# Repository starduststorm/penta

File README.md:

# penta

PCB designs and code for a Five-pointed star circumscribed within a circle of 55 pixels, for a total of 5³=125 pixels.

## Controls

The Five through-hole circles on the penta are touch-reactive and used to set the pattern.

## Hardware

* RP2040 dual-core ARM processor
* T3902 microphone
* WS2812B-1010 pixels

# Project layout

* board/ contains the KiCad pcb project
* src/ all project-specific source
* lib/ a skeleton copy of [kissfft], and submodule dependency *dustlib*

The project is built using [PlatformIO] in Visual Studio Code.

## Building

Build the v2 environment in the [PlatformIO] project, which corresponds to the MakerFaire2025 hardware.

You will likely need to run
```
git submodule update --init
```
in the source after ```git clone``` in order to fetch the submodule for building.

### Libraries & Dependencies
PlatformIO should fetch the apprpriate version of each dependency on first build.

* [FastLED] - A library for fast 8-bit math and rendering colors onto pixels
* [kissfft] - A simple library used to compute an fft on audio samples
* [dustlib] - My work-in-progress pixel library

[FastLED]: https://github.com/FastLED/FastLED
[PlatformIO]: <https://platformio.org>
[kissfft]: <https://github.com/mborgerding/kissfft>
[dustlib]: <https://github.com/starduststorm/dustlib>

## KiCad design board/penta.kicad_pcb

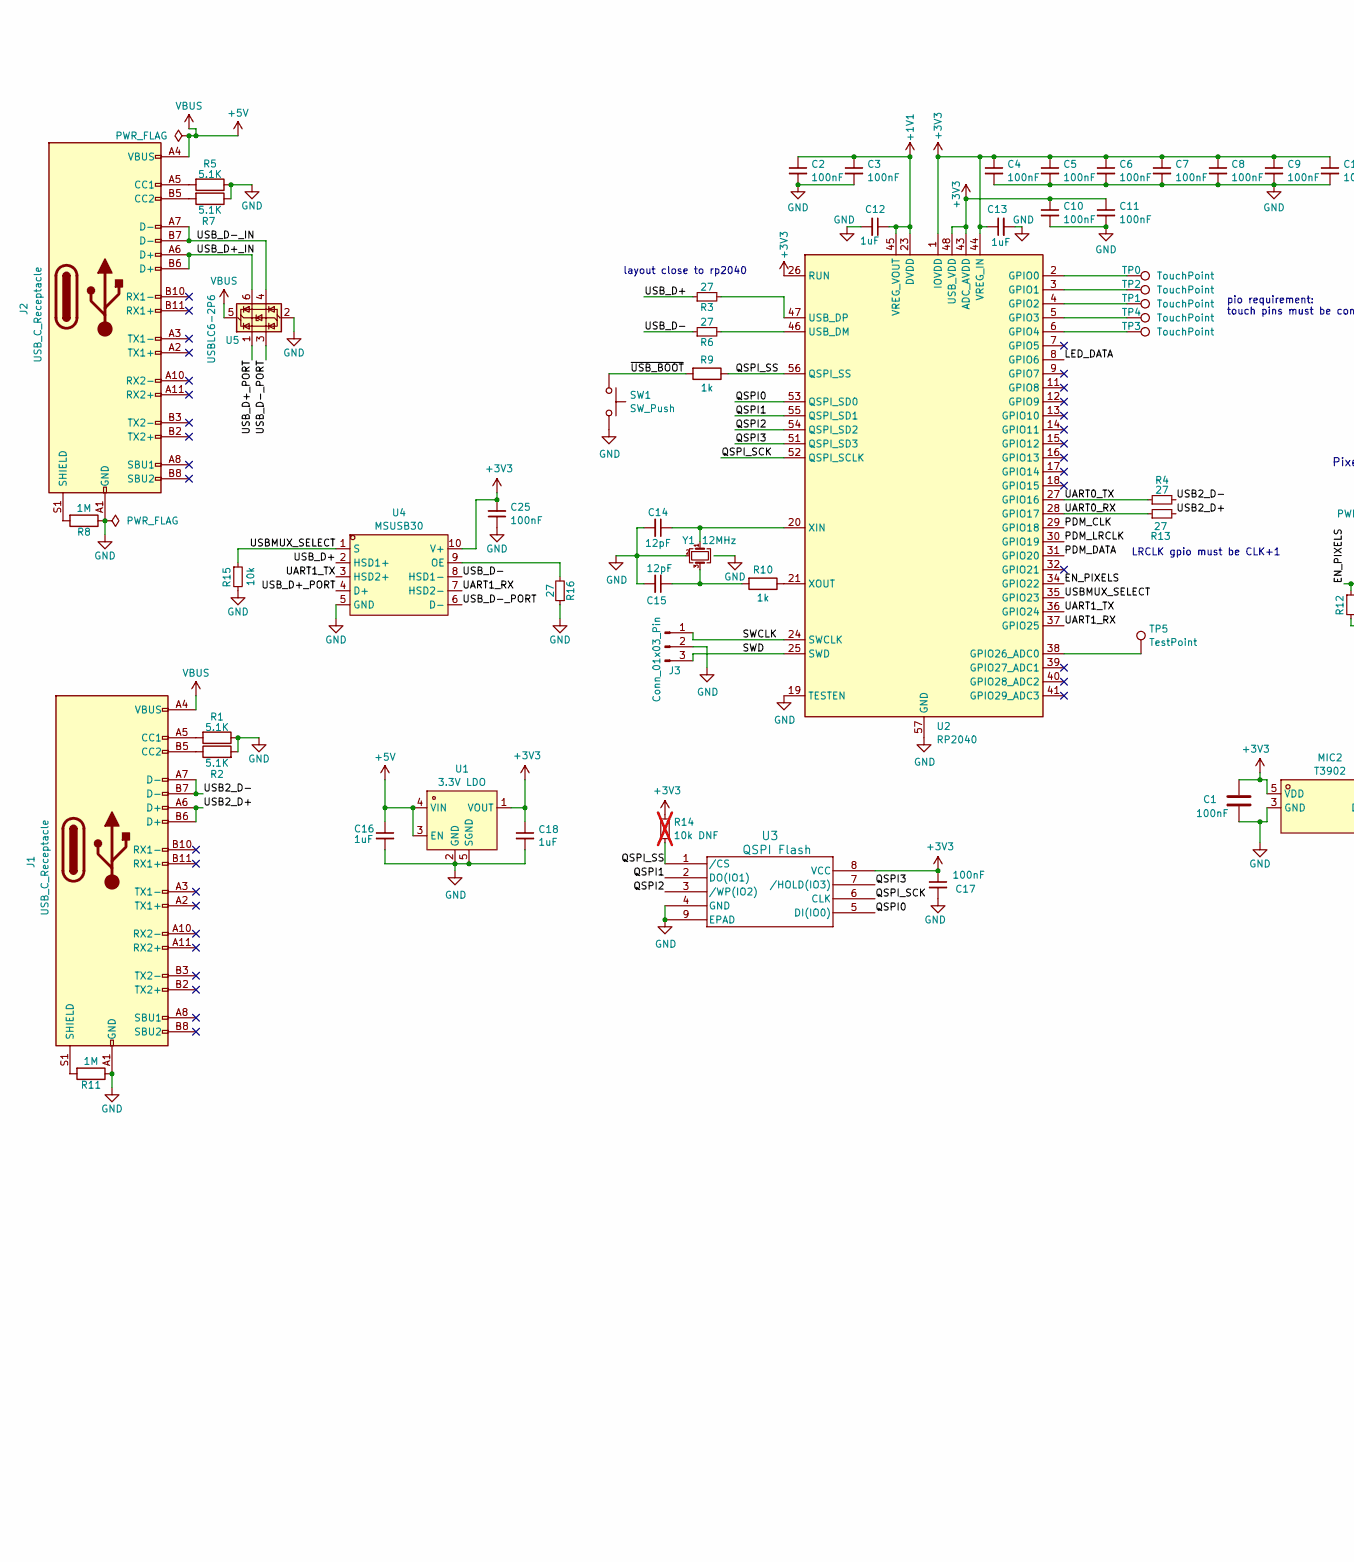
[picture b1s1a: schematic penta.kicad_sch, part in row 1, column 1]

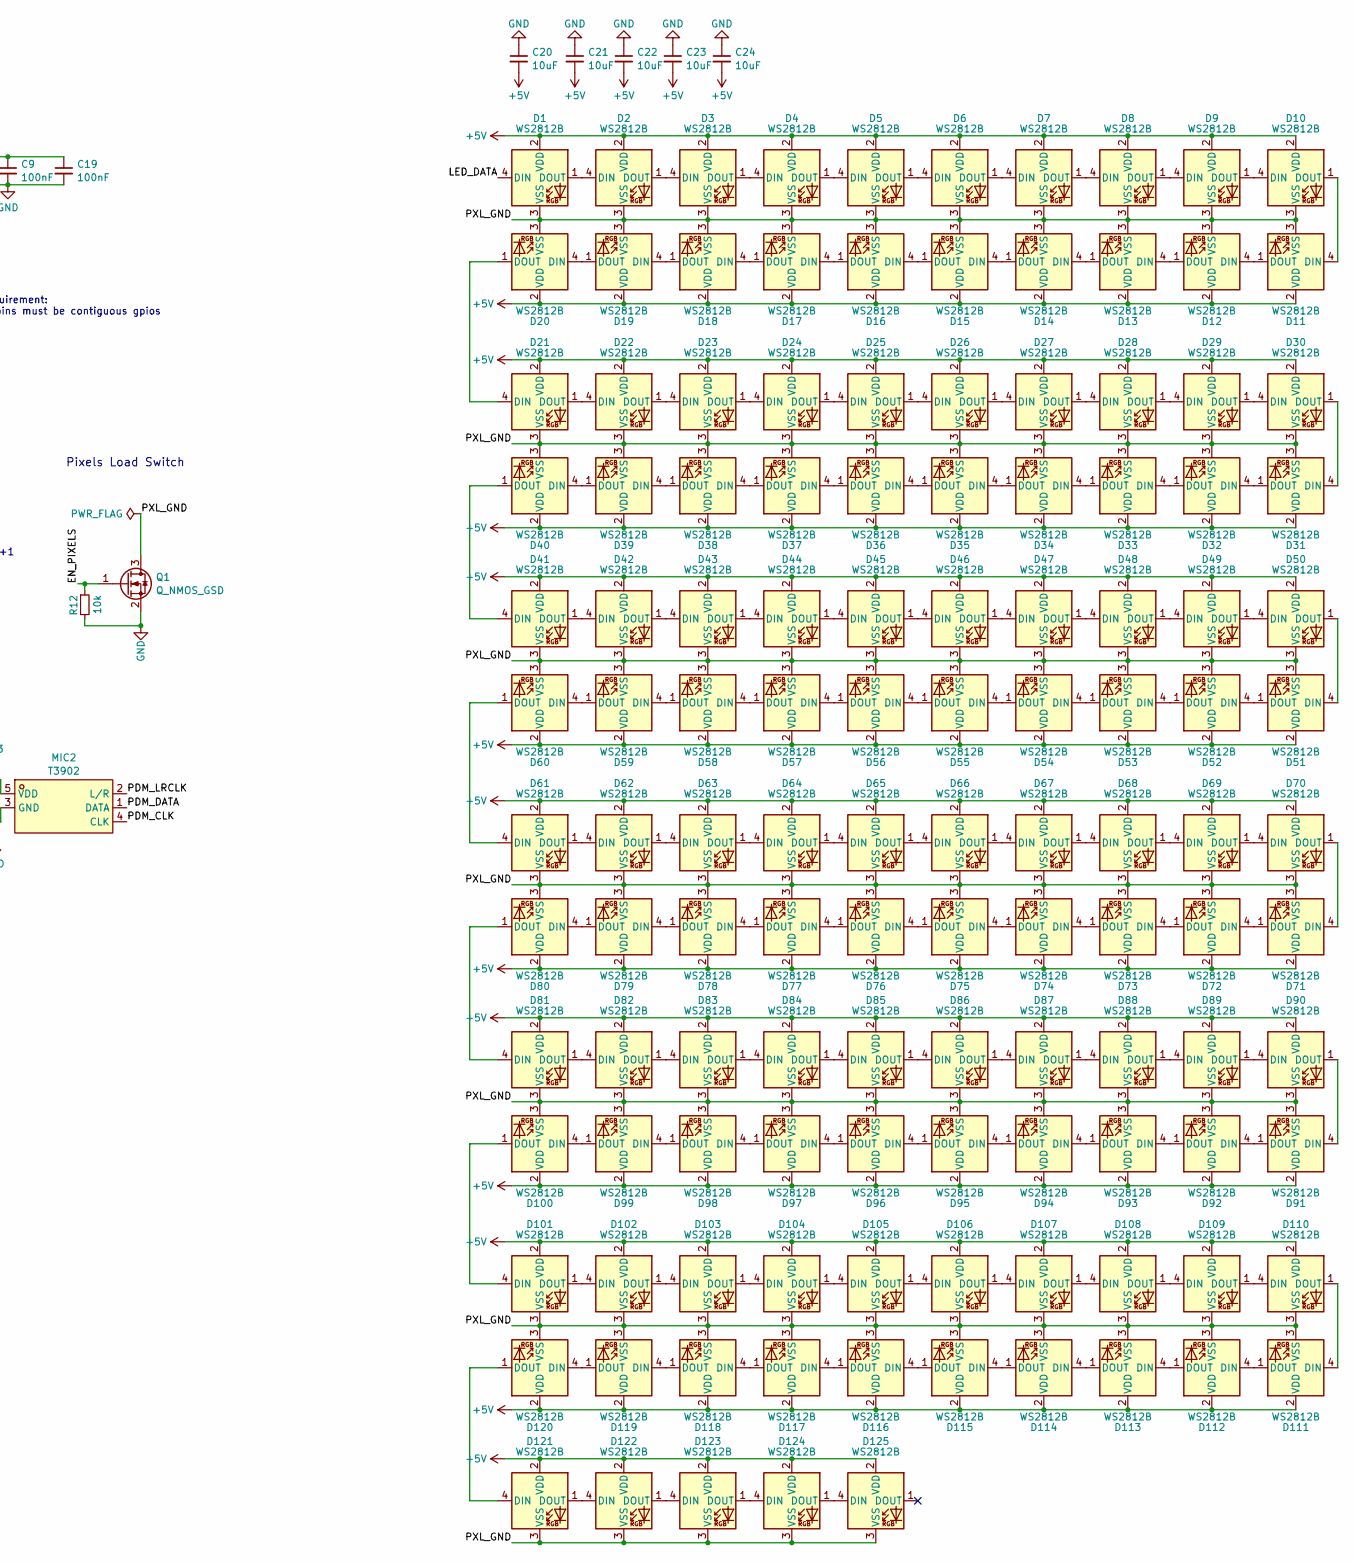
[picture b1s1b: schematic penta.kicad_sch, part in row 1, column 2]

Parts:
C1, C2, C3, C4, C5, C6, C7, C8, C9, C10, C11, C17, C19, C25: 100nF; C_0402_1005Metric; LCSC C1525
C12, C13, C16, C18: 1uF; C_0402_1005Metric; LCSC C52923
C14, C15: 12pF; C_0402_1005Metric; LCSC C1547
C20, C21, C22, C23, C24: 10uF; C_0402_1005Metric; LCSC C15525
D1, D2, D3, D4, D5, D6, D7, D8, D9, D10, D11, D12, D13, D14, D15, D16, D17, D18, D19, D20, D21, D22, D23, D24, D25, D26, D27, D28, D29, D30, D31, D32, D33, D34, D35, D36, D37, D38, D39, D40, D41, D42, D43, D44, D45, D46, D47, D48, D49, D50, D51, D52, D53, D54, D55, D56, D57, D58, D59, D60, D61, D62, D63, D64, D65, D66, D67, D68, D69, D70, D71, D72, D73, D74, D75, D76, D77, D78, D79, D80, D81, D82, D83, D84, D85, D86, D87, D88, D89, D90, D91, D92, D93, D94, D95, D96, D97, D98, D99, D100, D101, D102, D103, D104, D105, D106, D107, D108, D109, D110, D111, D112, D113, D114, D115, D116, D117, D118, D119, D120, D121, D122, D123, D124, D125: WS2812B; ws2812b_1010; LCSC C5349953
J1, J2: USB_C_Receptacle; USB-SMD_USB-TYPE-C-020; LCSC C2927040
J3: Conn_01x03_Pin; SMD_Pad_01x03_1.27mm
MIC2: T3902; MIC_T3902; LCSC Part C3171752
Q1: Q_NMOS_GSD; SOT-23
R1, R2, R5, R7: 5.1K; R_0402_1005Metric; LCSC C25905
R3, R4, R6, R13, R16: 27; R_0402_1005Metric; LCSC C138021
R8, R11: 1M; R_0402_1005Metric; LCSC C26083
R9, R10: 1k; R_0402_1005Metric; LCSC C11702
R12, R15: 10k; R_0402_1005Metric; LCSC C25744
R14: 10k DNF; R_0402_1005Metric; not fitted
SW1: SW_Push; KEY-SMD_L3.0-W2.5-LS4.0; LCSC C2905190
TP0, TP1, TP2, TP3, TP4: TouchPoint; ScrewTouchHole
TP5: TestPoint; TestPoint_Pad_D1.0mm
U1: 3.3V LDO; OnSemi_XDFN4-1EP_1.0x1.0mm_EP0.52x0.52mm; LCSC Part C147954
U2: RP2040; QFN-56-1EP_7x7mm_P0.4mm_EP3.2x3.2mm; LCSC C2040
U3: QSPI Flash; USON_3X2_WIN; LCSC C7304007
U4: MSUSB30; MSOP-10_3x3mm_P0.5mm; LCSC Part C231929
U5: USBLC6-2P6; SOT-666; LCSC C2827693
Y1: 12MHz; Crystal_SMD_2520-4Pin_2.5x2.0mm; LCSC C284155

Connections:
+1V1: C2.1, C3.1, C12.1, U2.23 (DVDD), U2.45 (VREG_VOUT), U2.50 (DVDD)
+3V3: C1.1, C4.1, C5.1, C6.1, C7.1, C8.1, C9.1, C10.1, C11.1, C13.1, C17.1, C18.1, C19.1, C25.2, MIC2.5 (VDD), R14.1, U1.1 (VOUT), U2.1 (IOVDD), U2.10 (IOVDD), U2.22 (IOVDD), U2.26 (RUN), U2.33 (IOVDD), U2.42 (IOVDD), U2.43 (ADC_AVDD), U2.44 (VREG_IN), U2.48 (USB_VDD), U2.49 (IOVDD), U3.8 (VCC), U4.10 (V+)
+5V: C16.1, C20.2, C21.2, C22.2, C23.2, C24.2, D1.2 (VDD), D2.2 (VDD), D3.2 (VDD), D4.2 (VDD), D5.2 (VDD), D6.2 (VDD), D7.2 (VDD), D8.2 (VDD), D9.2 (VDD), D10.2 (VDD), D11.2 (VDD), D12.2 (VDD), D13.2 (VDD), D14.2 (VDD), D15.2 (VDD), D16.2 (VDD), D17.2 (VDD), D18.2 (VDD), D19.2 (VDD), D20.2 (VDD), D21.2 (VDD), D22.2 (VDD), D23.2 (VDD), D24.2 (VDD), D25.2 (VDD), D26.2 (VDD), D27.2 (VDD), D28.2 (VDD), D29.2 (VDD), D30.2 (VDD), D31.2 (VDD), D32.2 (VDD), D33.2 (VDD), D34.2 (VDD), D35.2 (VDD), D36.2 (VDD), D37.2 (VDD), D38.2 (VDD), D39.2 (VDD), D40.2 (VDD), D41.2 (VDD), D42.2 (VDD), D43.2 (VDD), D44.2 (VDD), D45.2 (VDD), D46.2 (VDD), D47.2 (VDD), D48.2 (VDD), D49.2 (VDD), D50.2 (VDD), D51.2 (VDD), D52.2 (VDD), D53.2 (VDD), D54.2 (VDD), D55.2 (VDD), D56.2 (VDD), D57.2 (VDD), D58.2 (VDD), D59.2 (VDD), D60.2 (VDD), D61.2 (VDD), D62.2 (VDD), D63.2 (VDD), D64.2 (VDD), D65.2 (VDD), D66.2 (VDD), D67.2 (VDD), D68.2 (VDD), D69.2 (VDD), D70.2 (VDD), D71.2 (VDD), D72.2 (VDD), D73.2 (VDD), D74.2 (VDD), D75.2 (VDD), D76.2 (VDD), D77.2 (VDD), D78.2 (VDD), D79.2 (VDD), D80.2 (VDD), D81.2 (VDD), D82.2 (VDD), D83.2 (VDD), D84.2 (VDD), D85.2 (VDD), D86.2 (VDD), D87.2 (VDD), D88.2 (VDD), D89.2 (VDD), D90.2 (VDD), D91.2 (VDD), D92.2 (VDD), D93.2 (VDD), D94.2 (VDD), D95.2 (VDD), D96.2 (VDD), D97.2 (VDD), D98.2 (VDD), D99.2 (VDD), D100.2 (VDD), D101.2 (VDD), D102.2 (VDD), D103.2 (VDD), D104.2 (VDD), D105.2 (VDD), D106.2 (VDD), D107.2 (VDD), D108.2 (VDD), D109.2 (VDD), D110.2 (VDD), D111.2 (VDD), D112.2 (VDD), D113.2 (VDD), D114.2 (VDD), D115.2 (VDD), D116.2 (VDD), D117.2 (VDD), D118.2 (VDD), D119.2 (VDD), D120.2 (VDD), D121.2 (VDD), D122.2 (VDD), D123.2 (VDD), D124.2 (VDD), D125.2 (VDD), J1.A4 (VBUS), J1.A9 (VBUS), J1.B4 (VBUS), J1.B9 (VBUS), J2.A4 (VBUS), J2.A9 (VBUS), J2.B4 (VBUS), J2.B9 (VBUS), U1.3 (EN), U1.4 (VIN), U5.5 (VBUS)
/EN_PIXELS: Q1.1 (G), R12.1, U2.34 (GPIO22)
/LED_DATA: D1.4 (DIN), U2.8 (GPIO6)
/PDM_CLK: MIC2.4 (CLK), U2.29 (GPIO18)
/PDM_DATA: MIC2.1 (DATA), U2.31 (GPIO20)
/PDM_LRCLK: MIC2.2 (L/R), U2.30 (GPIO19)
/PXL_GND: D1.3 (VSS), D2.3 (VSS), D3.3 (VSS), D4.3 (VSS), D5.3 (VSS), D6.3 (VSS), D7.3 (VSS), D8.3 (VSS), D9.3 (VSS), D10.3 (VSS), D11.3 (VSS), D12.3 (VSS), D13.3 (VSS), D14.3 (VSS), D15.3 (VSS), D16.3 (VSS), D17.3 (VSS), D18.3 (VSS), D19.3 (VSS), D20.3 (VSS), D21.3 (VSS), D22.3 (VSS), D23.3 (VSS), D24.3 (VSS), D25.3 (VSS), D26.3 (VSS), D27.3 (VSS), D28.3 (VSS), D29.3 (VSS), D30.3 (VSS), D31.3 (VSS), D32.3 (VSS), D33.3 (VSS), D34.3 (VSS), D35.3 (VSS), D36.3 (VSS), D37.3 (VSS), D38.3 (VSS), D39.3 (VSS), D40.3 (VSS), D41.3 (VSS), D42.3 (VSS), D43.3 (VSS), D44.3 (VSS), D45.3 (VSS), D46.3 (VSS), D47.3 (VSS), D48.3 (VSS), D49.3 (VSS), D50.3 (VSS), D51.3 (VSS), D52.3 (VSS), D53.3 (VSS), D54.3 (VSS), D55.3 (VSS), D56.3 (VSS), D57.3 (VSS), D58.3 (VSS), D59.3 (VSS), D60.3 (VSS), D61.3 (VSS), D62.3 (VSS), D63.3 (VSS), D64.3 (VSS), D65.3 (VSS), D66.3 (VSS), D67.3 (VSS), D68.3 (VSS), D69.3 (VSS), D70.3 (VSS), D71.3 (VSS), D72.3 (VSS), D73.3 (VSS), D74.3 (VSS), D75.3 (VSS), D76.3 (VSS), D77.3 (VSS), D78.3 (VSS), D79.3 (VSS), D80.3 (VSS), D81.3 (VSS), D82.3 (VSS), D83.3 (VSS), D84.3 (VSS), D85.3 (VSS), D86.3 (VSS), D87.3 (VSS), D88.3 (VSS), D89.3 (VSS), D90.3 (VSS), D91.3 (VSS), D92.3 (VSS), D93.3 (VSS), D94.3 (VSS), D95.3 (VSS), D96.3 (VSS), D97.3 (VSS), D98.3 (VSS), D99.3 (VSS), D100.3 (VSS), D101.3 (VSS), D102.3 (VSS), D103.3 (VSS), D104.3 (VSS), D105.3 (VSS), D106.3 (VSS), D107.3 (VSS), D108.3 (VSS), D109.3 (VSS), D110.3 (VSS), D111.3 (VSS), D112.3 (VSS), D113.3 (VSS), D114.3 (VSS), D115.3 (VSS), D116.3 (VSS), D117.3 (VSS), D118.3 (VSS), D119.3 (VSS), D120.3 (VSS), D121.3 (VSS), D122.3 (VSS), D123.3 (VSS), D124.3 (VSS), D125.3 (VSS), Q1.3 (D)
/QSPI0: U2.53 (QSPI_SD0), U3.5 (DI(IO0))
/QSPI1: U2.55 (QSPI_SD1), U3.2 (DO(IO1))
/QSPI2: U2.54 (QSPI_SD2), U3.3 (/WP(IO2))
/QSPI3: U2.51 (QSPI_SD3), U3.7 (/HOLD(IO3))
/QSPI_SCK: U2.52 (QSPI_SCLK), U3.6 (CLK)
/QSPI_SS: R9.1, R14.2, U2.56 (QSPI_SS), U3.1 (/CS)
/SWCLK: J3.1, U2.24 (SWCLK)
/SWD: J3.3, U2.25 (SWD)
/UART0_RX: R13.1, U2.28 (GPIO17)
/UART0_TX: R4.1, U2.27 (GPIO16)
/UART1_RX: U2.37 (GPIO25), U4.7 (HSD2-)
/UART1_TX: U2.36 (GPIO24), U4.3 (HSD2+)
/USB2_D+: J1.A6 (D+), J1.B6 (D+), R13.2
/USB2_D-: J1.A7 (D-), J1.B7 (D-), R4.2
/USBMUX_SELECT: R15.1, U2.35 (GPIO23), U4.1 (S)
/USB_D+: R3.1, U4.2 (HSD1+)
/USB_D+_IN: J2.A6 (D+), J2.B6 (D+), U5.6 (I/O1)
/USB_D+_PORT: U4.4 (D+), U5.1 (I/O1)
/USB_D-: R6.1, U4.8 (HSD1-)
/USB_D-_IN: J2.A7 (D-), J2.B7 (D-), U5.4 (I/O2)
/USB_D-_PORT: U4.6 (D-), U5.3 (I/O2)
/~USB_BOOT: R9.2, SW1.1
GND: C1.2, C2.2, C3.2, C4.2, C5.2, C6.2, C7.2, C8.2, C9.2, C10.2, C11.2, C12.2, C13.2, C14.2, C15.2, C16.2, C17.2, C18.2, C19.2, C20.1, C21.1, C22.1, C23.1, C24.1, C25.1, J1.A1 (GND), J1.A12 (GND), J1.B1 (GND), J1.B12 (GND), J2.A1 (GND), J2.A12 (GND), J2.B1 (GND), J2.B12 (GND), J3.2, MIC2.3 (GND), Q1.2 (S), R1.1, R2.2, R5.1, R7.1, R8.1, R11.1, R12.2, R15.2, R16.1, SW1.2, U1.2 (GND), U1.5 (SGND), U2.19 (TESTEN), U2.57 (GND), U3.4 (GND), U3.9 (EPAD), U4.5 (GND), U5.2 (GND), Y1.2 (G), Y1.4 (G)
unnamed: C15.1, R10.2, Y1.3
unnamed: D1.1 (DOUT), D2.4 (DIN)
unnamed: D2.1 (DOUT), D3.4 (DIN)
unnamed: D3.1 (DOUT), D4.4 (DIN)
unnamed: D4.1 (DOUT), D5.4 (DIN)
unnamed: D5.1 (DOUT), D6.4 (DIN)
unnamed: D6.1 (DOUT), D7.4 (DIN)
unnamed: D7.1 (DOUT), D8.4 (DIN)
unnamed: D8.1 (DOUT), D9.4 (DIN)
unnamed: D9.1 (DOUT), D10.4 (DIN)
unnamed: D10.1 (DOUT), D11.4 (DIN)
unnamed: D11.1 (DOUT), D12.4 (DIN)
unnamed: D12.1 (DOUT), D13.4 (DIN)
unnamed: D13.1 (DOUT), D14.4 (DIN)
unnamed: D14.1 (DOUT), D15.4 (DIN)
unnamed: D15.1 (DOUT), D16.4 (DIN)
unnamed: D16.1 (DOUT), D17.4 (DIN)
unnamed: D17.1 (DOUT), D18.4 (DIN)
unnamed: D18.1 (DOUT), D19.4 (DIN)
unnamed: D19.1 (DOUT), D20.4 (DIN)
unnamed: D20.1 (DOUT), D21.4 (DIN)
unnamed: D21.1 (DOUT), D22.4 (DIN)
unnamed: D22.1 (DOUT), D23.4 (DIN)
unnamed: D23.1 (DOUT), D24.4 (DIN)
unnamed: D24.1 (DOUT), D25.4 (DIN)
unnamed: D25.1 (DOUT), D26.4 (DIN)
unnamed: D26.1 (DOUT), D27.4 (DIN)
unnamed: D27.1 (DOUT), D28.4 (DIN)
unnamed: D28.1 (DOUT), D29.4 (DIN)
unnamed: D29.1 (DOUT), D30.4 (DIN)
unnamed: D30.1 (DOUT), D31.4 (DIN)
unnamed: D31.1 (DOUT), D32.4 (DIN)
unnamed: D32.1 (DOUT), D33.4 (DIN)
unnamed: D33.1 (DOUT), D34.4 (DIN)
unnamed: D34.1 (DOUT), D35.4 (DIN)
unnamed: D35.1 (DOUT), D36.4 (DIN)
unnamed: D36.1 (DOUT), D37.4 (DIN)
unnamed: D37.1 (DOUT), D38.4 (DIN)
unnamed: D38.1 (DOUT), D39.4 (DIN)
unnamed: D39.1 (DOUT), D40.4 (DIN)
unnamed: D40.1 (DOUT), D41.4 (DIN)
unnamed: D41.1 (DOUT), D42.4 (DIN)
unnamed: D42.1 (DOUT), D43.4 (DIN)
unnamed: D43.1 (DOUT), D44.4 (DIN)
unnamed: D44.1 (DOUT), D45.4 (DIN)
unnamed: D45.1 (DOUT), D46.4 (DIN)
unnamed: D46.1 (DOUT), D47.4 (DIN)
unnamed: D47.1 (DOUT), D48.4 (DIN)
unnamed: D48.1 (DOUT), D49.4 (DIN)
unnamed: D49.1 (DOUT), D50.4 (DIN)
unnamed: D50.1 (DOUT), D51.4 (DIN)
unnamed: D51.1 (DOUT), D52.4 (DIN)
unnamed: D52.1 (DOUT), D53.4 (DIN)
unnamed: D53.1 (DOUT), D54.4 (DIN)
unnamed: D54.1 (DOUT), D55.4 (DIN)
unnamed: D55.1 (DOUT), D56.4 (DIN)
unnamed: D56.1 (DOUT), D57.4 (DIN)
unnamed: D57.1 (DOUT), D58.4 (DIN)
unnamed: D58.1 (DOUT), D59.4 (DIN)
unnamed: D59.1 (DOUT), D60.4 (DIN)
unnamed: D60.1 (DOUT), D61.4 (DIN)
unnamed: D61.1 (DOUT), D62.4 (DIN)
unnamed: D62.1 (DOUT), D63.4 (DIN)
unnamed: D63.1 (DOUT), D64.4 (DIN)
unnamed: D64.1 (DOUT), D65.4 (DIN)
unnamed: D65.1 (DOUT), D66.4 (DIN)
unnamed: D66.1 (DOUT), D67.4 (DIN)
unnamed: D67.1 (DOUT), D68.4 (DIN)
unnamed: D68.1 (DOUT), D69.4 (DIN)
unnamed: D69.1 (DOUT), D70.4 (DIN)
unnamed: D70.1 (DOUT), D71.4 (DIN)
unnamed: D71.1 (DOUT), D72.4 (DIN)
unnamed: D72.1 (DOUT), D73.4 (DIN)
unnamed: D73.1 (DOUT), D74.4 (DIN)
unnamed: D74.1 (DOUT), D75.4 (DIN)
unnamed: D75.1 (DOUT), D76.4 (DIN)
unnamed: D76.1 (DOUT), D77.4 (DIN)
unnamed: D77.1 (DOUT), D78.4 (DIN)
unnamed: D78.1 (DOUT), D79.4 (DIN)
unnamed: D79.1 (DOUT), D80.4 (DIN)
unnamed: D80.1 (DOUT), D81.4 (DIN)
unnamed: D81.1 (DOUT), D82.4 (DIN)
unnamed: D82.1 (DOUT), D83.4 (DIN)
unnamed: D83.1 (DOUT), D84.4 (DIN)
unnamed: D84.1 (DOUT), D85.4 (DIN)
unnamed: D85.1 (DOUT), D86.4 (DIN)
unnamed: D86.1 (DOUT), D87.4 (DIN)
unnamed: D87.1 (DOUT), D88.4 (DIN)
unnamed: D88.1 (DOUT), D89.4 (DIN)
unnamed: D89.1 (DOUT), D90.4 (DIN)
unnamed: D90.1 (DOUT), D91.4 (DIN)
unnamed: D91.1 (DOUT), D92.4 (DIN)
unnamed: D92.1 (DOUT), D93.4 (DIN)
unnamed: D93.1 (DOUT), D94.4 (DIN)
unnamed: D94.1 (DOUT), D95.4 (DIN)
unnamed: D95.1 (DOUT), D96.4 (DIN)
unnamed: D96.1 (DOUT), D97.4 (DIN)
unnamed: D97.1 (DOUT), D98.4 (DIN)
unnamed: D98.1 (DOUT), D99.4 (DIN)
unnamed: D99.1 (DOUT), D100.4 (DIN)
unnamed: D100.1 (DOUT), D101.4 (DIN)
unnamed: D101.1 (DOUT), D102.4 (DIN)
unnamed: D102.1 (DOUT), D103.4 (DIN)
unnamed: D103.1 (DOUT), D104.4 (DIN)
unnamed: D104.1 (DOUT), D105.4 (DIN)
unnamed: D105.1 (DOUT), D106.4 (DIN)
unnamed: D106.1 (DOUT), D107.4 (DIN)
unnamed: D107.1 (DOUT), D108.4 (DIN)
unnamed: D108.1 (DOUT), D109.4 (DIN)
unnamed: D109.1 (DOUT), D110.4 (DIN)
unnamed: D110.1 (DOUT), D111.4 (DIN)
unnamed: D111.1 (DOUT), D112.4 (DIN)
unnamed: D112.1 (DOUT), D113.4 (DIN)
unnamed: D113.1 (DOUT), D114.4 (DIN)
unnamed: D114.1 (DOUT), D115.4 (DIN)
unnamed: D115.1 (DOUT), D116.4 (DIN)
unnamed: D116.1 (DOUT), D117.4 (DIN)
unnamed: D117.1 (DOUT), D118.4 (DIN)
unnamed: D118.1 (DOUT), D119.4 (DIN)
unnamed: D119.1 (DOUT), D120.4 (DIN)
unnamed: D120.1 (DOUT), D121.4 (DIN)
unnamed: D121.1 (DOUT), D122.4 (DIN)
unnamed: D122.1 (DOUT), D123.4 (DIN)
unnamed: D123.1 (DOUT), D124.4 (DIN)
unnamed: D124.1 (DOUT), D125.4 (DIN)
unnamed: J1.A5 (CC1), R1.2
unnamed: J1.B5 (CC2), R2.1
unnamed: J1.S1 (SHIELD), R11.2
unnamed: J2.A5 (CC1), R5.2
unnamed: J2.B5 (CC2), R7.2
unnamed: J2.S1 (SHIELD), R8.2
unnamed: TP0.1, U2.2 (GPIO0)
unnamed: TP2.1, U2.3 (GPIO1)
unnamed: TP1.1, U2.4 (GPIO2)
unnamed: TP4.1, U2.5 (GPIO3)
unnamed: TP3.1, U2.6 (GPIO4)
unnamed: TP5.1, U2.38 (GPIO26_ADC0)
unnamed: R6.2, U2.46 (USB_DM)
unnamed: R3.2, U2.47 (USB_DP)
unnamed: C14.1, U2.20 (XIN), Y1.1
unnamed: R10.1, U2.21 (XOUT)
unnamed: R16.2, U4.9 (OE)

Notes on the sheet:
layout close to rp2040
LRCLK gpio must be CLK+1
Pixels Load Switch
pio requirement: touch pins must be contiguous gpios

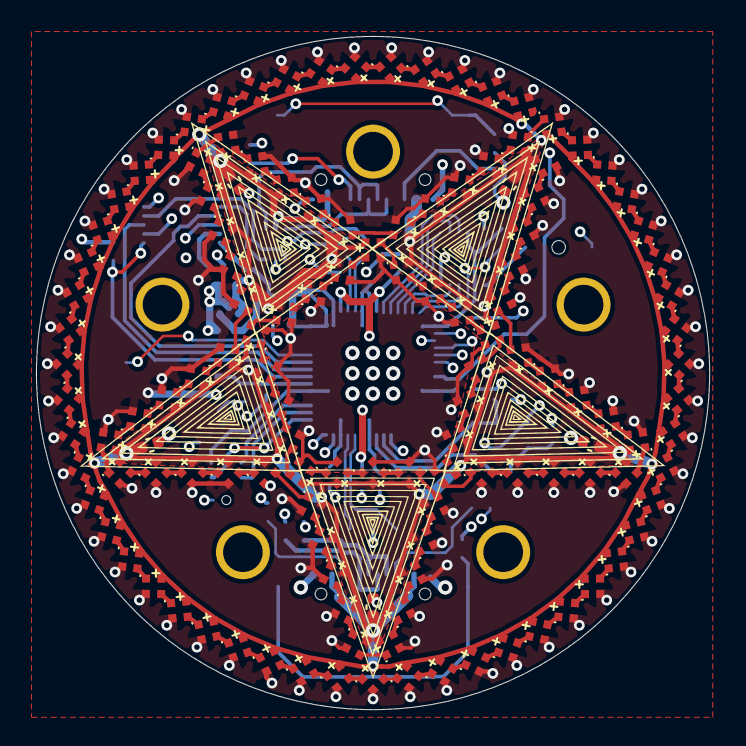
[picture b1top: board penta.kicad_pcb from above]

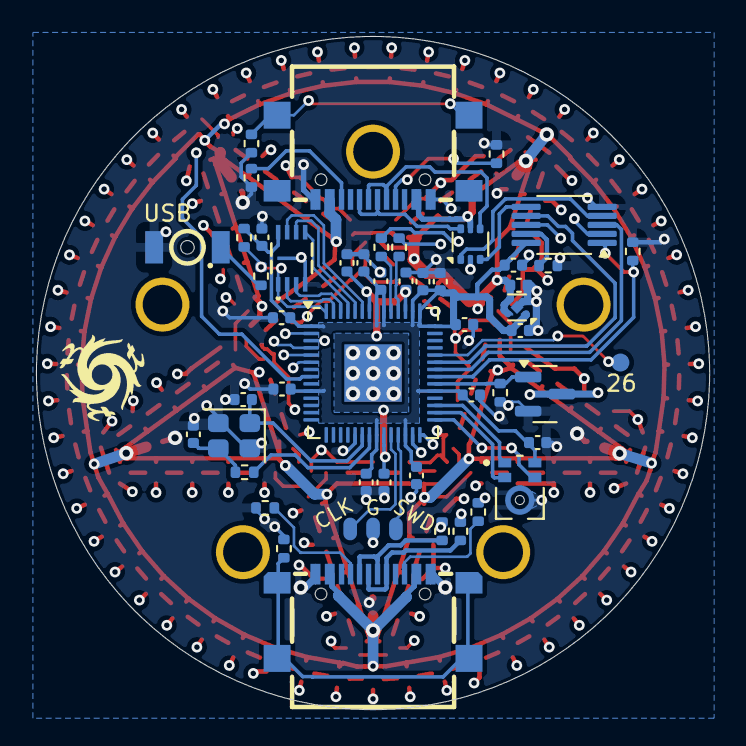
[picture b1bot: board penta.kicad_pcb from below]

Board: 4 copper layers, 37.4 x 37.4 mm, 184 parts (49 on the bottom side), 174 nets.

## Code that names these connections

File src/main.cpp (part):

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
#if HARDWARE_VERSION >= 2

#define LED_DATA 6
#define LED_LINE_0_POWER 22

#define USBMUX_SELECT 23
#define UART0_TX 16
#define UART0_RX 17

#define UART1_TX 24
#define UART1_RX 25

#define PIN_PDM_DIN 20
#define PIN_PDM_CLK 18

#define UNCONNECTED_PIN_1 27
#define UNCONNECTED_PIN_2 28

#elif HARDWARE_VERSION == 1

#define LED_DATA 26
#define LED_LINE_0_POWER 27

#define PIN_PDM_DIN 6
#define PIN_PDM_CLK 28

#define UNCONNECTED_PIN_1 7
#define UNCONNECTED_PIN_2 7
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
#include <audio.h>

// The T3902's select pin (PDM_LRCLK, GPIO19) has no pull on the board, so it
// must be driven or each unit's mic picks a clock edge at random and some read
// as a flat line. Drive it HIGH (dustlib's fixSelectHIGH) -- the level the
// arduino-pico PDM sampler expects.
AudioInputPDM audioInput(PIN_PDM_DIN, PIN_PDM_CLK, /*fixSelectHIGH*/ true);
FFTProcessing fftProcessing(audioInput, 10, 128);
// keeps the mic streaming amplitude measurements for sound patterns' run conditions
AmplitudeReceiver *ambientSound = NULL;
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  // fighting a 10k to ground the pin must still read low. If it reads high the
  // pulldown is missing and the mux floats whenever we aren't driving it, e.g.
  // in the bootloader.
  gpio_init(USBMUX_SELECT);
  gpio_pull_up(USBMUX_SELECT);
  delayMicroseconds(100);
  selectPulledLow = !gpio_get(USBMUX_SELECT);
  gpio_disable_pulls(USBMUX_SELECT);
  logf("usb mux select pulldown R15: %s", selectPulledLow ? "present" : "MISSING -- floats high");

  // Route the shared USB-C port through the mux: LOW = RP2040 USB, HIGH = UART1.
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
    if (pixelsNeedPower) {
      // reset the pin after using it for gpio (assume fastled on pio0)
      gpio_set_function(LED_DATA, GPIO_FUNC_PIO0);
    } else {
      // we low-side switch, so when the gnd is disconnected, a small amount of curent is still flowing thru pixel 0 data line, which is driven low from drawing #000000
      assert(gpio_get_function(LED_DATA) == GPIO_FUNC_PIO0, "LED_DATA not PIO?");
      pinMode(LED_DATA, OUTPUT);
      gpio_put(LED_DATA, true);
    }
  }

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
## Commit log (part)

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2023-11-15 initial pixel layout concept
2023-12-06 candidate pixel layout + RP2040 + microphone + USB
2023-12-08 remove the 5v net
2023-12-24 schematic for a boost chip that we may not actually need; + wc changes
2025-01-11 completely rework everything but the pixels; base it off seeeduino for ease/cost; add a usb port for chaining; add a microphone
2025-01-11 myriad improvements. mounting points for idk, nice symmetric. removed unnecessary pads from seeduino footprint to make room for mount points; added exposed ldo VIN pin to seeduino footprint bc it's V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
2025-01-11 add 3 gpios to the screwmounts, which are now thts. maybe these can be used for capacitive touch?
2025-01-15 add an nfet so we can power down pixels for whatever saves that'll get doing larger pattern work; make 4-layer board to support switching a gnd plane off; decorate
2025-01-15 make a real quick usb coupler intended to be printed on flexible pcb
2025-01-16 src stubs with tested-and-working rp2040 gpio touch pins via pio
2025-01-16 platformio.ini
2025-01-16 pins rearrangement to make touch pads work; minor fixes and polish
2025-01-16 ok. support all 5 touch pins because we can
2025-01-17 exclude touch fps from bom
2025-01-17 add a hopefully-more-bendable spot to the usb coupler; fix drc; add sds
2025-01-25 candidate designs for ded and deh couplers
2025-01-29 pixel mapping; basic patterns; functional on live hardware
2025-01-29 layout on ded to make it a little shorter and give the thts a little more space
2025-01-29 ded: add stiffener layer
2025-01-29 basic tap selection for color/index state (requires dustlib changes)
2025-01-31 checkpoint: BitsFiller fixes for split mode, added some new options, add continueTo edgeType for bits to move thru intersections; new patterns FiveBitsPattern, BreadthFirstPattern, TrianglePointSourc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
2025-01-31 make TrianglePointSource better; start working on a better button scheme
2025-02-12 ded stiffener fixes from last week's production rev
2025-02-13 some wips fiddling with auto mode and interactions; tweaks
2025-02-18 add submodules
2025-02-19 fix a long-standing FIXME involving particle fade-up, where fadeup didn't work with random path selection; should also improve performance at the cost of some memory, though I have not measured this
2025-02-19 change BitsFiller fadeDown to be per 1/256 millisecond for finer-grained fadeDown configuration; use it + the new fadeUp improvements to make the BreadthFirst pattern look less frenetic
2025-03-08 factor Graph and BitsFiller into dustlib and adopt the new version
2025-03-08 add a really nice new smooth colors patter based on the improved particle fadeup; add some todos
2025-05-18 add a WIP audio input & processing class situation, for later inclusion in dustlib; fftprocessing via kissfft; bring over soundbits from evm - it looks pretty good
2025-08-16 drop in an rp2040 and associated circuitry; proper usb port (two of them); bottom-facing mic; do a first pass on layout
2025-09-02 add a usb mux for communicating between pentas and make a draft layout
2025-09-03 polish & readiness
2025-09-03 exclude swd pins from pos file
2025-09-16 commit some code i mostly wrote months ago but never felt was finished. this reworks the touch button system to toggle on or off FIVE periodic patterns, along with some animations to soft of indicate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
2025-09-16 v2 bringup
2025-09-24 disable turning the pixels on and off because it's not fully working
2025-09-25 disable automode because it's not ready / requires multiple pentas; add an arrow bits instead, which toggles on and off on long press
2025-09-28 dismiss the long-press arrow animations when changing modes, because it's too confusing how to turn them off when there are multiple lit; also default v2 build
2025-10-01 remove FastLED and kissfft as submodules - we'll use FastLED as a library in PlatformIO, and include a skeleton copy of kissfft directly (since the full version's psdpng.c does not build against rp20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
2025-10-01 add skeleton of kissfft
2025-10-01 basic readme
2025-10-01 instructions for building a fresh clone
2025-10-02 am i awake? who is to tell.
2025-11-17 kissfft copy needs licenses
2026-03-25 fix powering pixels on and off as needed
